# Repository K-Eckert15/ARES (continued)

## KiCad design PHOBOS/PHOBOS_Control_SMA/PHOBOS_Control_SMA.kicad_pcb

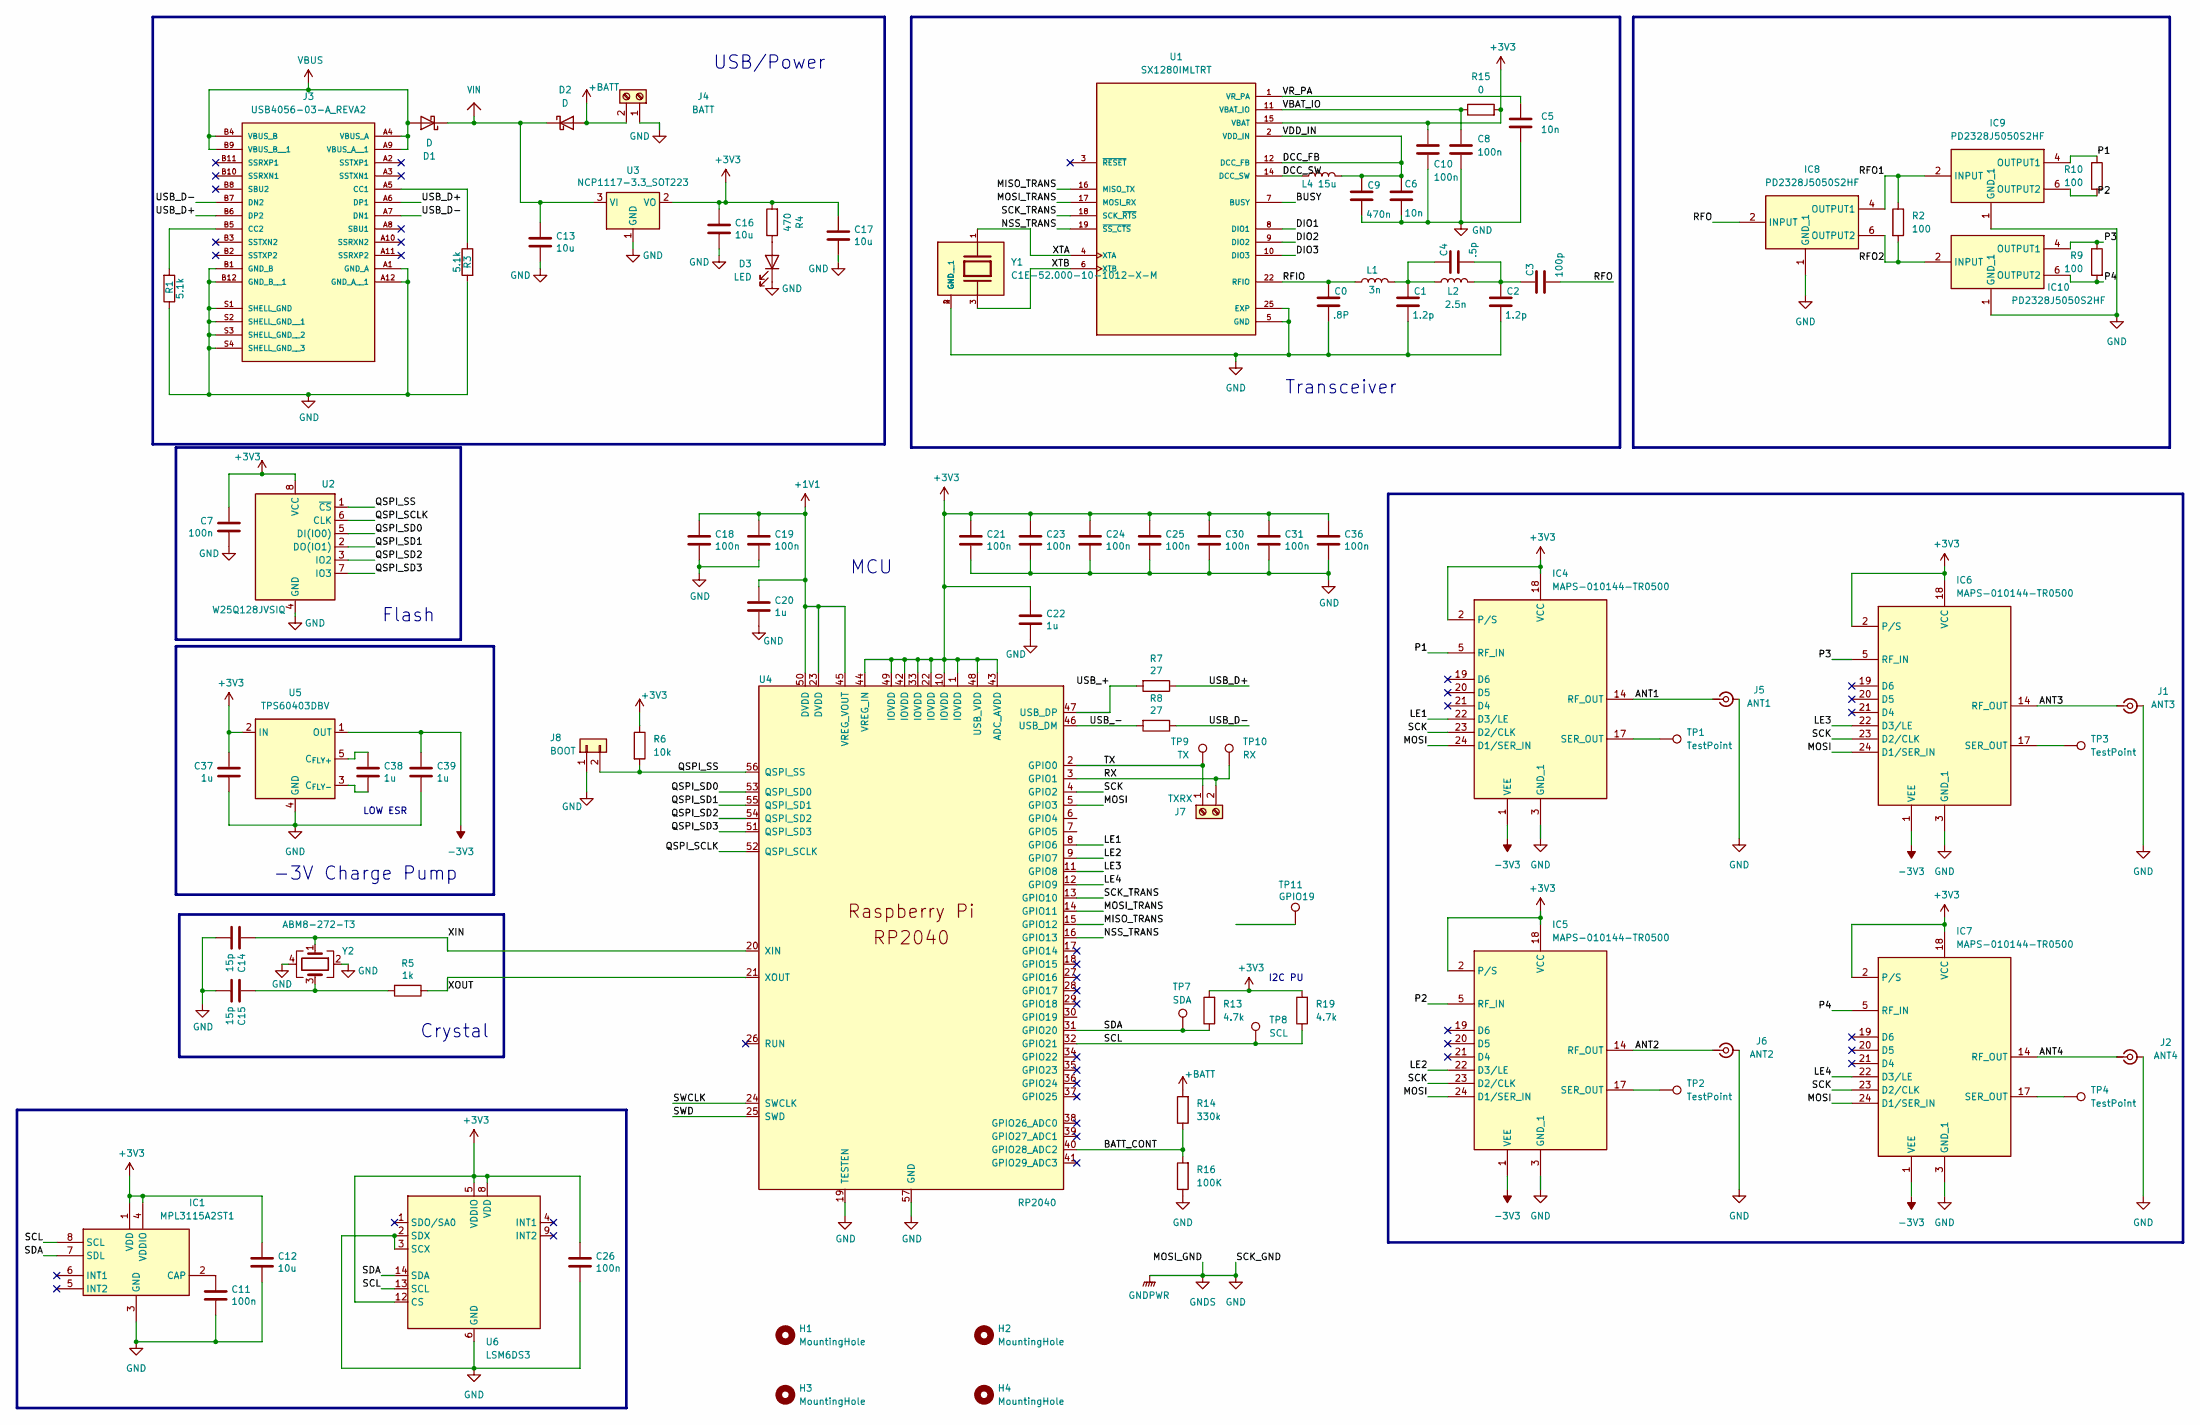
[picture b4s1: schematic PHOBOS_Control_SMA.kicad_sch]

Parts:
C0: .8P; C_0402_1005Metric_Pad0.74x0.62mm_HandSolder; MFG # GRM1555C1HR80BA01D
C1, C2: 1.2p; C_0402_1005Metric_Pad0.74x0.62mm_HandSolder; MFG # GRM1555C1H1R2BA01D
C3: 100p; C_0402_1005Metric_Pad0.74x0.62mm_HandSolder; MFG # GRM1555C1H101JA01D
C4: .5p; C_0402_1005Metric_Pad0.74x0.62mm_HandSolder; MFG # GRM1555C1HR50WA01D
C5, C6: 10n; C_0402_1005Metric_Pad0.74x0.62mm_HandSolder; MFG # GRM155R71E103KA01D
C7, C11, C18, C19, C21, C23, C24, C25, C26, C30, C31, C36: 100n; C_0402_1005Metric; MFG # CL05B104KO5NNNC
C8, C10: 100n; C_0402_1005Metric_Pad0.74x0.62mm_HandSolder; MFG # GRM155R71C104KA88D
C9: 470n; C_0402_1005Metric_Pad0.74x0.62mm_HandSolder; MFG # GRM155R61A474KE15D
C12, C13, C16, C17: 10u; C_0603_1608Metric_Pad1.08x0.95mm_HandSolder; MFG # CL10X106MO8NRNC
C14, C15: 15p; C_0402_1005Metric; MFG # GJM1555C1H150GB01D
C20, C22: 1u; C_0402_1005Metric; MFG # C0603X5R500-105KNP-CT
C37, C38, C39: 1u; C_0603_1608Metric; MFG # C0603X5R500-105KNP-CT
D1, D2: D; D_0603_1608Metric_Pad1.05x0.95mm_HandSolder; MFG # CD0603-B0340R
D3: LED; LED_0603_1608Metric_Pad1.05x0.95mm_HandSolder; MFG # QBLP601-IB5-S2897
H1, H2, H3, H4: MountingHole; MountingHole_3.2mm_M3
IC1: MPL3115A2ST1; Manufacturer_Part_Number MPL3115A2ST1; Mouser Part Number 771-MPL3115A2ST1
IC4, IC5, IC6, IC7: MAPS-010144-TR0500; QFN50P400X400X100-25N-D; Mouser Part Number 937-MAPS-010144T5
IC8, IC9, IC10: PD2328J5050S2HF; Mouser Part Number 620-PD2328J5050S2HF
J1: ANT3; SAMTEC_SMA-J-P-GF-RA-SM1
J2: ANT4; SAMTEC_SMA-J-P-GF-RA-SM1
J3: USB4056-03-A_REVA2; GCT_USB4056-03-A_REVA2; PARTREV A2
J4: BATT; TerminalBlock_4Ucon_1x02_P3.50mm_Horizontal; MFG # OSTTE020104
J5: ANT1; SAMTEC_SMA-J-P-GF-RA-SM1
J6: ANT2; SAMTEC_SMA-J-P-GF-RA-SM1
J7: TXRX; TerminalBlock_4Ucon_1x02_P3.50mm_Horizontal; MFG # OSTTE020104
J8: BOOT; PinHeader_1x02_P2.54mm_Vertical
L1: 3n; L_0402_1005Metric_Pad0.77x0.64mm_HandSolder; MFG # LQW15AN3N0B80D
L2: 2.5n; L_0402_1005Metric_Pad0.77x0.64mm_HandSolder; MFG # LQW15AN2N5C00D
L4: 15u; L_0805_2012Metric_Pad1.05x1.20mm_HandSolder; MFG # MLZ2012M150W
R1, R3: 5.1k; R_0402_1005Metric; MFG # AC0402FR-7W5K1L
R2, R9, R10: 100; R_0603_1608Metric
R4: 470; R_0402_1005Metric; MFG # AC0402FR-7W470RL
R5: 1k; R_0402_1005Metric; MFG # AC0402FR-7W1KL
R6: 10k; R_0402_1005Metric; MFG # AC0402FR-7W10KL
R7, R8: 27; R_0402_1005Metric; MFG # RC0402FR-7W27RL
R13, R19: 4.7k; R_0402_1005Metric; MFG # AC0402FR-7W4K7L
R14: 330k; R_0402_1005Metric; MFG # CRGCQ0402F330K
R15: 0; R_0402_1005Metric_Pad0.72x0.64mm_HandSolder; MFG # CRCW04020000Z0ED
R16: 100K; R_0402_1005Metric; MFG # AC0402FR-7W100KL
TP1, TP2, TP3, TP4: TestPoint; Pin_D1.0mm_L10.0mm
TP7: SDA; TestPoint_THTPad_D2.0mm_Drill1.0mm
TP8: SCL; TestPoint_THTPad_D2.0mm_Drill1.0mm
TP9: TX; TestPoint_THTPad_D2.0mm_Drill1.0mm
TP10: RX; TestPoint_THTPad_D2.0mm_Drill1.0mm
TP11: GPIO19; TestPoint_THTPad_D2.0mm_Drill1.0mm
U1: SX1280IMLTRT; XCVR_SX1280IMLTRT; PARTREV 3.3
U2: W25Q128JVSIQ; SOIC-8_5.3x5.3mm_P1.27mm; MFG # W25Q128JVSIQ
U3: NCP1117-3.3_SOT223; SOT-223-3_TabPin2; MFG # NCP1117ST33T3G
U4: RP2040; QFN-56-1EP_7x7mm_P0.4mm_EP3.2x3.2mm; MFG # SC0914(13)
U5: TPS60403DBV; SOT-23-5; MFG # TPS60403DBV
U6: LSM6DS3; LGA-14_3x2.5mm_P0.5mm_LayoutBorder3x4y
Y1: C1E-52.000-10-1012-X-M; XTAL_C1E-52.000-10-1012-X-M; PARTREV August 01, 2022
Y2: ABM8-272-T3; Crystal_SMD_3225-4Pin_3.2x2.5mm; MFG # ABM8-272-T3

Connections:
+1V1: C18.1, C19.1, C20.1, U4.23 (DVDD), U4.45 (VREG_VOUT), U4.50 (DVDD)
+3V3: C7.1, C10.1, C12.1, C16.1, C17.1, C21.1, C22.1, C23.1, C24.1, C25.1, C26.1, C30.1, C31.1, C36.1, C37.1, IC1.1 (VDD), IC1.4 (VDDIO), IC4.2 (P/S), IC4.18 (VCC), IC5.2 (P/S), IC5.18 (VCC), IC6.2 (P/S), IC6.18 (VCC), IC7.2 (P/S), IC7.18 (VCC), R4.2, R6.1, R13.2, R15.2, R19.2, U1.15 (VBAT), U2.8 (VCC), U3.2 (VO), U4.1 (IOVDD), U4.10 (IOVDD), U4.22 (IOVDD), U4.33 (IOVDD), U4.42 (IOVDD), U4.43 (ADC_AVDD), U4.44 (VREG_IN), U4.48 (USB_VDD), U4.49 (IOVDD), U5.2 (IN), U6.5 (VDDIO), U6.8 (VDD), U6.12 (CS)
+BATT: D2.2 (A), J4.2, R14.2
-3V3: C39.1, IC4.1 (VEE), IC5.1 (VEE), IC6.1 (VEE), IC7.1 (VEE), U5.1 (OUT)
/ANT1: IC4.14 (RF_OUT), J5.1 (In)
/ANT2: IC5.14 (RF_OUT), J6.1 (In)
/ANT3: IC6.14 (RF_OUT), J1.1 (In)
/ANT4: IC7.14 (RF_OUT), J2.1 (In)
/BATT_CONT: R14.1, R16.2, U4.40 (GPIO28_ADC2)
/BUSY: U1.7 (BUSY)
/DCC_FB: C6.1, C9.1, L4.2, U1.2 (VDD_IN), U1.12 (DCC_FB)
/DCC_SW: L4.1, U1.14 (DCC_SW)
/DIO1: U1.8 (DIO1)
/DIO2: U1.9 (DIO2)
/DIO3: U1.10 (DIO3)
/LE1: IC4.22 (D3/LE), U4.8 (GPIO6)
/LE2: IC5.22 (D3/LE), U4.9 (GPIO7)
/LE3: IC6.22 (D3/LE), U4.11 (GPIO8)
/LE4: IC7.22 (D3/LE), U4.12 (GPIO9)
/MISO_TRANS: U1.16 (MISO_TX), U4.15 (GPIO12)
/MOSI: IC4.24 (D1/SER_IN), IC5.24 (D1/SER_IN), IC6.24 (D1/SER_IN), IC7.24 (D1/SER_IN), U4.5 (GPIO3)
/MOSI_TRANS: U1.17 (MOSI_RX), U4.14 (GPIO11)
/NSS_TRANS: U1.19 (~SS_CTS), U4.16 (GPIO13)
/P1: IC4.5 (RF_IN), IC9.4 (OUTPUT1), R10.1
/P2: IC5.5 (RF_IN), IC9.6 (OUTPUT2), R10.2
/P3: IC6.5 (RF_IN), IC10.4 (OUTPUT1), R9.1
/P4: IC7.5 (RF_IN), IC10.6 (OUTPUT2), R9.2
/QSPI_SCLK: U2.6 (CLK), U4.52 (QSPI_SCLK)
/QSPI_SD0: U2.5 (DI(IO0)), U4.53 (QSPI_SD0)
/QSPI_SD1: U2.2 (DO(IO1)), U4.55 (QSPI_SD1)
/QSPI_SD2: U2.3 (IO2), U4.54 (QSPI_SD2)
/QSPI_SD3: U2.7 (IO3), U4.51 (QSPI_SD3)
/QSPI_SS: J8.2, R6.2, U2.1 (~CS), U4.56 (QSPI_SS)
/RFIO: C0.1, L1.1, U1.22 (RFIO)
/RFO: C3.2, IC8.2 (INPUT)
/RFO1: IC8.4 (OUTPUT1), IC9.2 (INPUT), R2.1
/RFO2: IC8.6 (OUTPUT2), IC10.2 (INPUT), R2.2
/RX: J7.2, TP10.1 (1_1), U4.3 (GPIO1)
/SCK: IC4.23 (D2/CLK), IC5.23 (D2/CLK), IC6.23 (D2/CLK), IC7.23 (D2/CLK), U4.4 (GPIO2)
/SCK_TRANS: U1.18 (SCK_~RTS), U4.13 (GPIO10)
/SCL: IC1.8 (SCL), R19.1, TP8.1 (1_1), U4.32 (GPIO21), U6.13 (SCL)
/SDA: IC1.7 (SDL), R13.1, TP7.1 (1_1), U4.31 (GPIO20), U6.14 (SDA)
/SWCLK: U4.24 (SWCLK)
/SWD: U4.25 (SWD)
/TX: J7.1, TP9.1 (1_1), U4.2 (GPIO0)
/USB_+: R7.2, U4.47 (USB_DP)
/USB_-: R8.2, U4.46 (USB_DM)
/USB_D+: J3.A6 (DP1), J3.B6 (DP2), R7.1
/USB_D-: J3.A7 (DN1), J3.B7 (DN2), R8.1
/VBAT_IO: C8.1, R15.1, U1.11 (VBAT_IO)
/VR_PA: C5.1, U1.1 (VR_PA)
/XIN: C14.1, U4.20 (XIN), Y2.1
/XOUT: R5.1, U4.21 (XOUT)
/XTA: U1.4 (XTA), Y1.1
/XTB: U1.6 (XTB), Y1.3
GND: C0.2, C1.2, C2.2, C5.2, C6.2, C7.2, C8.2, C9.2, C10.2, C11.2, C12.2, C13.2, C14.2, C15.2, C16.2, C17.2, C18.2, C19.2, C20.2, C21.2, C22.2, C23.2, C24.2, C25.2, C26.2, C30.2, C31.2, C36.2, C37.2, C39.2, D3.1 (K), IC1.3 (GND), IC4.3 (GND_1), IC4.4 (GND_2), IC4.6 (GND_3), IC4.7 (GND_4), IC4.8 (GND_5), IC4.9 (GND_6), IC4.10 (GND_7), IC4.11 (GND_8), IC4.12 (GND_9), IC4.13 (GND_10), IC4.15 (GND_11), IC4.16 (GND_12), IC4.25 (GND_13), IC5.3 (GND_1), IC5.4 (GND_2), IC5.6 (GND_3), IC5.7 (GND_4), IC5.8 (GND_5), IC5.9 (GND_6), IC5.10 (GND_7), IC5.11 (GND_8), IC5.12 (GND_9), IC5.13 (GND_10), IC5.15 (GND_11), IC5.16 (GND_12), IC5.25 (GND_13), IC6.3 (GND_1), IC6.4 (GND_2), IC6.6 (GND_3), IC6.7 (GND_4), IC6.8 (GND_5), IC6.9 (GND_6), IC6.10 (GND_7), IC6.11 (GND_8), IC6.12 (GND_9), IC6.13 (GND_10), IC6.15 (GND_11), IC6.16 (GND_12), IC6.25 (GND_13), IC7.3 (GND_1), IC7.4 (GND_2), IC7.6 (GND_3), IC7.7 (GND_4), IC7.8 (GND_5), IC7.9 (GND_6), IC7.10 (GND_7), IC7.11 (GND_8), IC7.12 (GND_9), IC7.13 (GND_10), IC7.15 (GND_11), IC7.16 (GND_12), IC7.25 (GND_13), IC8.1 (GND_1), IC8.3 (GND_2), IC8.5 (GND_3), IC9.1 (GND_1), IC9.3 (GND_2), IC9.5 (GND_3), IC10.1 (GND_1), IC10.3 (GND_2), IC10.5 (GND_3), J1.2 (Ext), J2.2 (Ext), J3.A1 (GND_A), J3.A12 (GND_A__1), J3.B1 (GND_B), J3.B12 (GND_B__1), J3.S1 (SHELL_GND), J3.S2 (SHELL_GND__1), J3.S3 (SHELL_GND__2), J3.S4 (SHELL_GND__3), J4.1, J5.2 (Ext), J6.2 (Ext), J8.1, R1.1, R3.2, R16.1, U1.5 (GND), U1.13 (GND), U1.20 (GND), U1.21 (GND), U1.23 (GND), U1.24 (GND), U1.25 (EXP), U2.4 (GND), U3.1 (GND), U4.19 (TESTEN), U4.57 (GND), U5.4 (GND), U6.2 (SDX), U6.3 (SCX), U6.6 (GND), U6.7 (GND), Y1.2 (GND), Y1.4 (GND__1), Y2.2, Y2.4
unnamed: C1.1, C4.1, L1.2, L2.1
unnamed: C2.1, C3.1, C4.2, L2.2
unnamed: C15.1, R5.2, Y2.3
unnamed: D3.2 (A), R4.1
unnamed: C11.1, IC1.2 (CAP)
unnamed: IC4.17 (SER_OUT), TP1.1
unnamed: IC5.17 (SER_OUT), TP2.1
unnamed: IC6.17 (SER_OUT), TP3.1
unnamed: IC7.17 (SER_OUT), TP4.1
unnamed: J3.A5 (CC1), R3.1
unnamed: J3.B5 (CC2), R1.2
unnamed: C38.1, U5.5 (C_{FLY+})
unnamed: C38.2, U5.3 (C_{FLY-})
VBUS: D1.2 (A), J3.A4 (VBUS_A), J3.A9 (VBUS_A__1), J3.B4 (VBUS_B), J3.B9 (VBUS_B__1)
VIN: C13.1, D1.1 (K), D2.1 (K), U3.3 (VI)

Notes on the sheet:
Transceiver
-3V Charge Pump
LOW ESR
Flash
Crystal
MCU
I2C PU
USB/Power

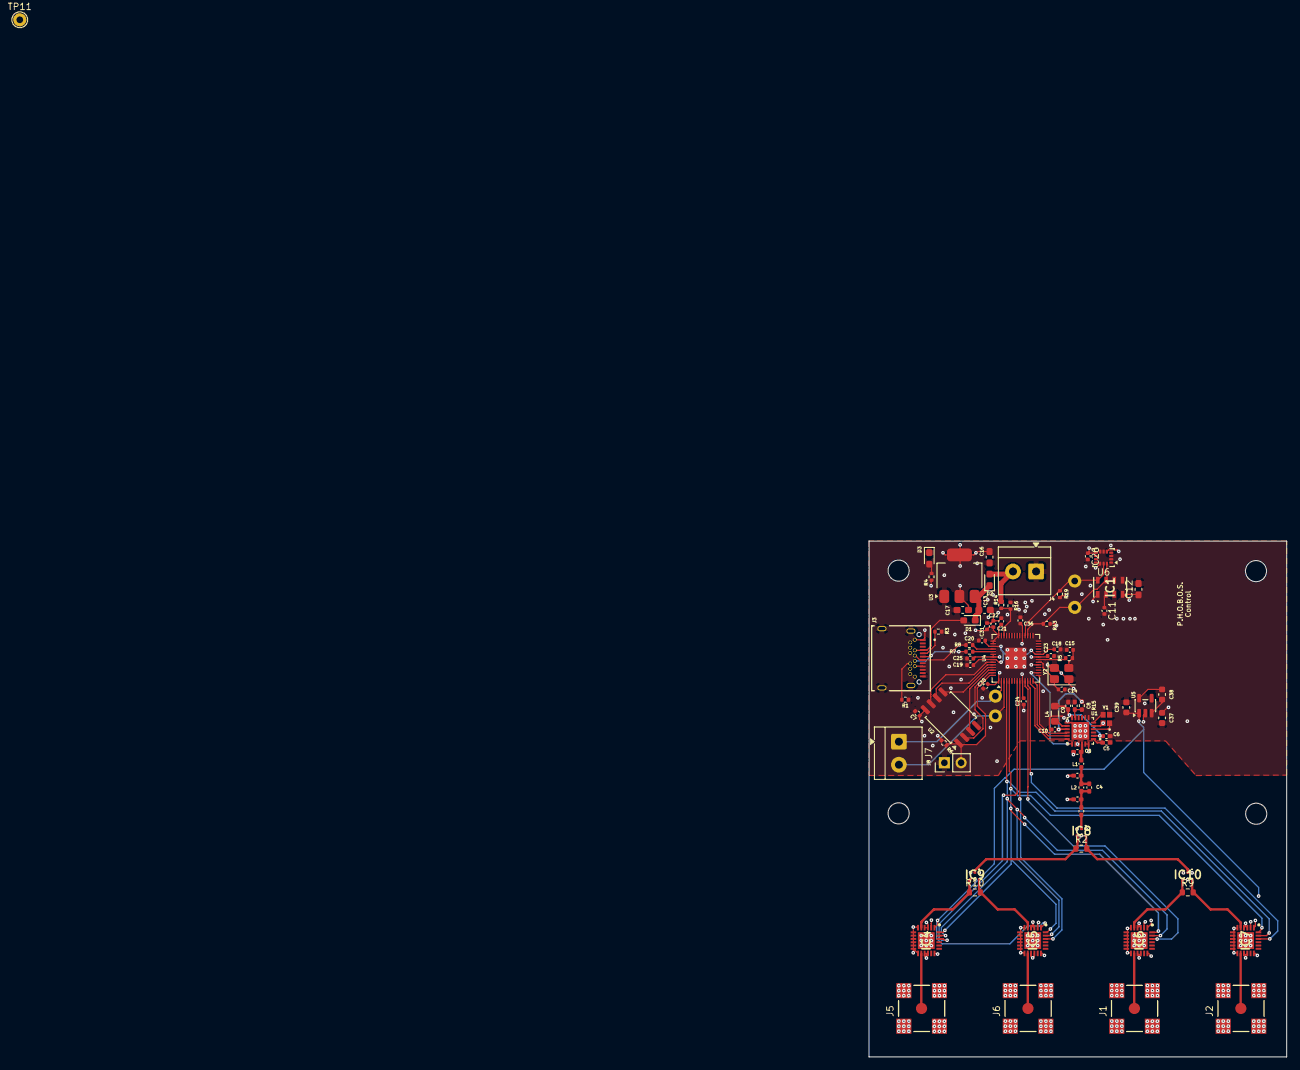
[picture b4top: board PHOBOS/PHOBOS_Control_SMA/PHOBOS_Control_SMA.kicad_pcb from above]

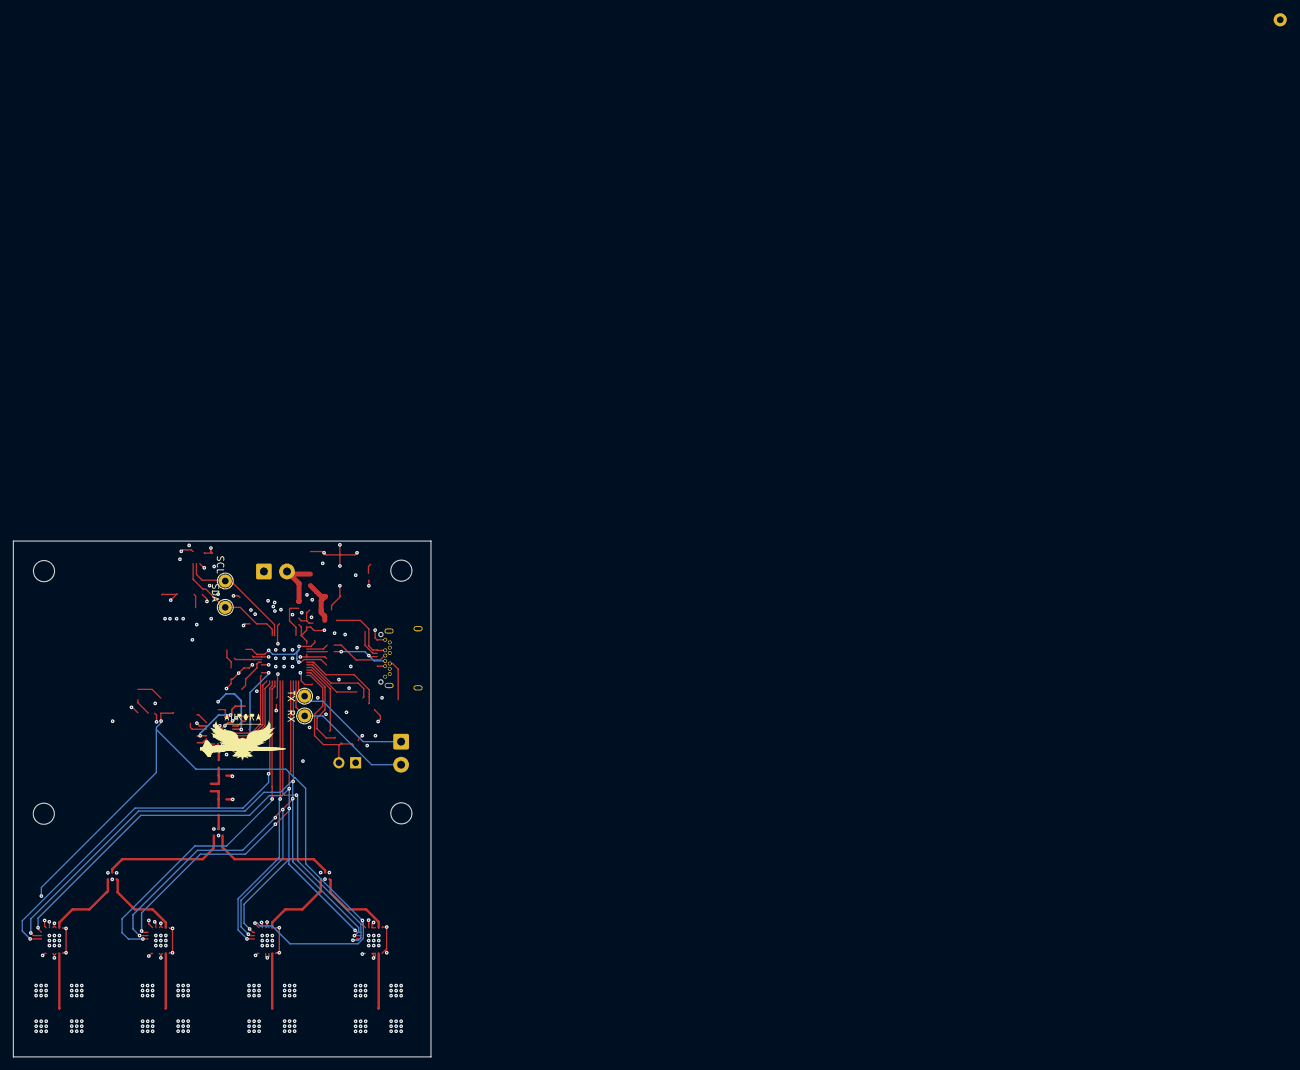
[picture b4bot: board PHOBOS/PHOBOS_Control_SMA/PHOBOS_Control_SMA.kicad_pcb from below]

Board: 4 copper layers, 63.4 x 78.3 mm, 87 parts (4 on the bottom side), 61 nets.

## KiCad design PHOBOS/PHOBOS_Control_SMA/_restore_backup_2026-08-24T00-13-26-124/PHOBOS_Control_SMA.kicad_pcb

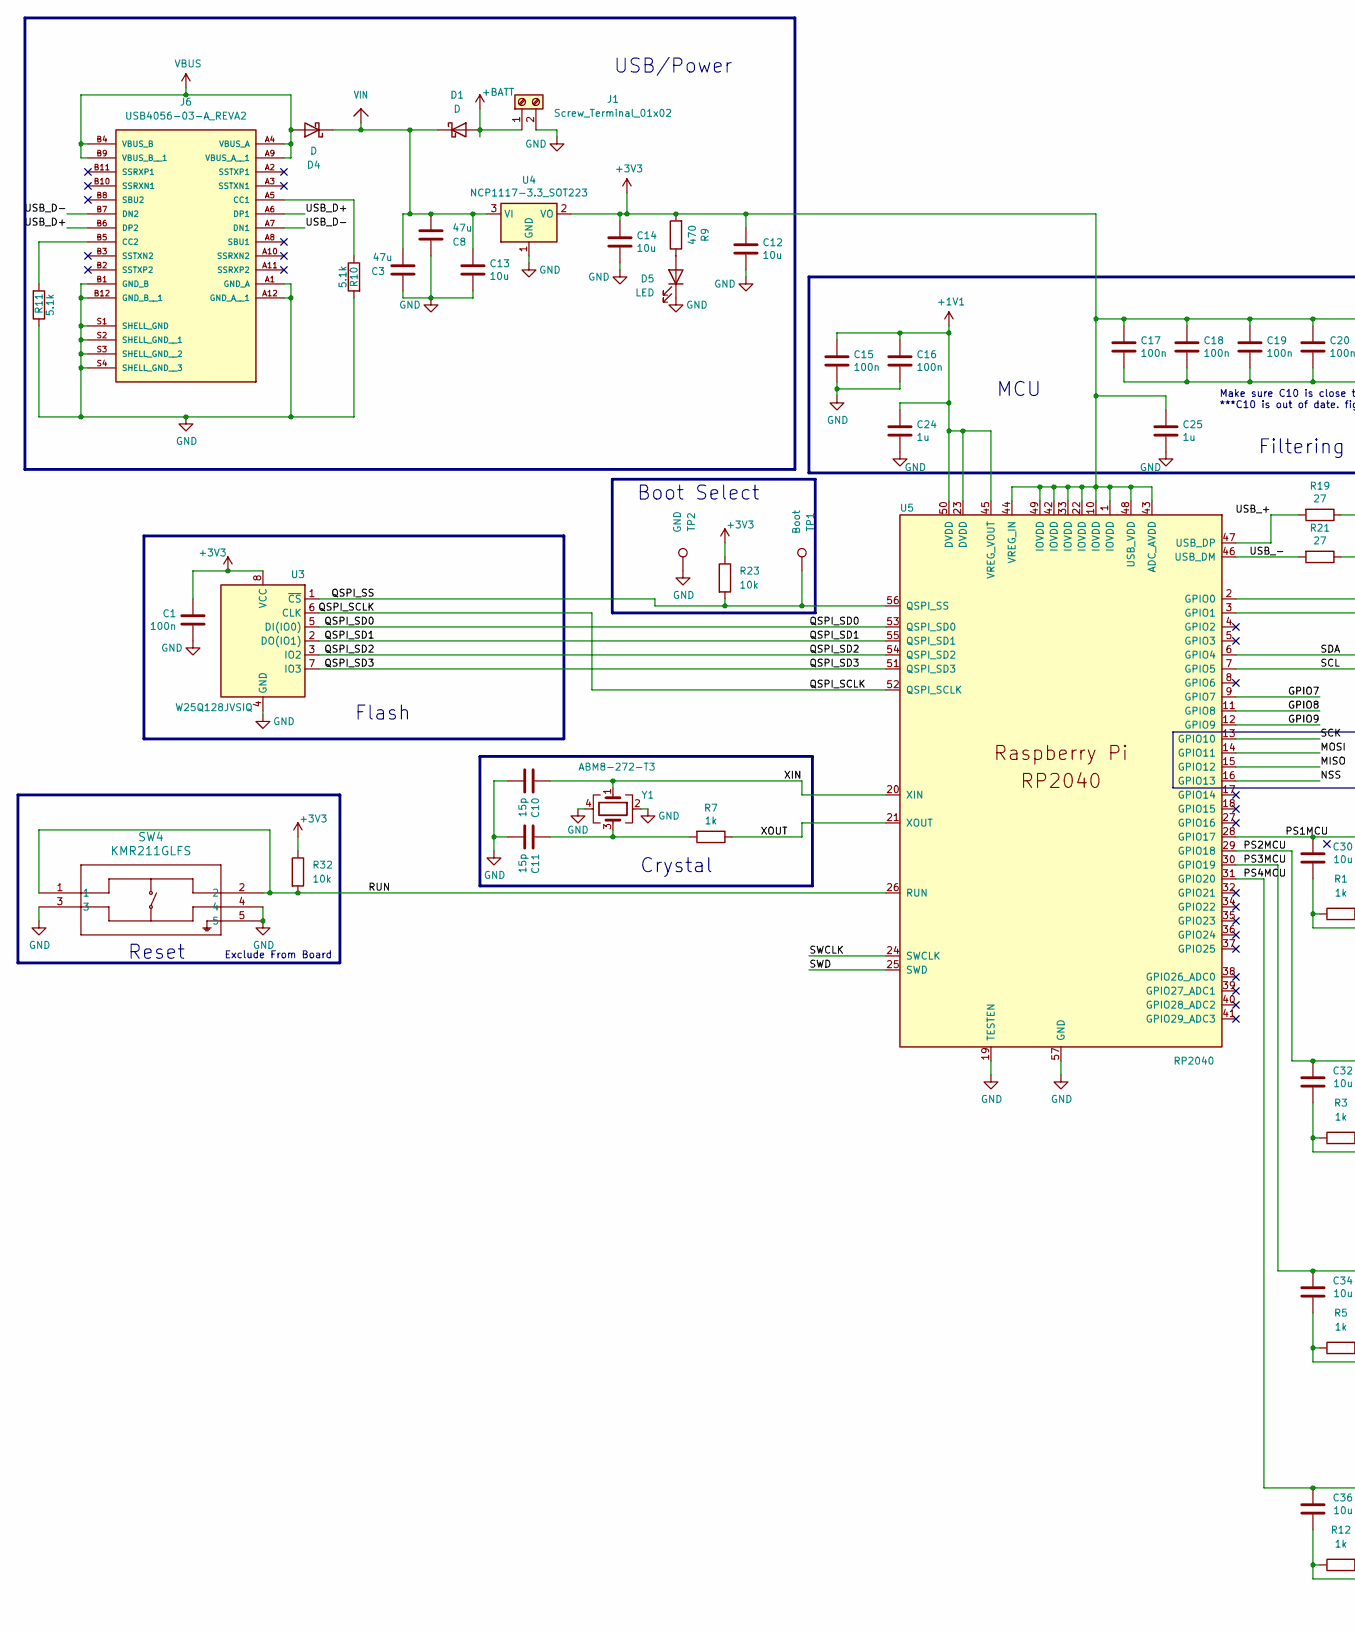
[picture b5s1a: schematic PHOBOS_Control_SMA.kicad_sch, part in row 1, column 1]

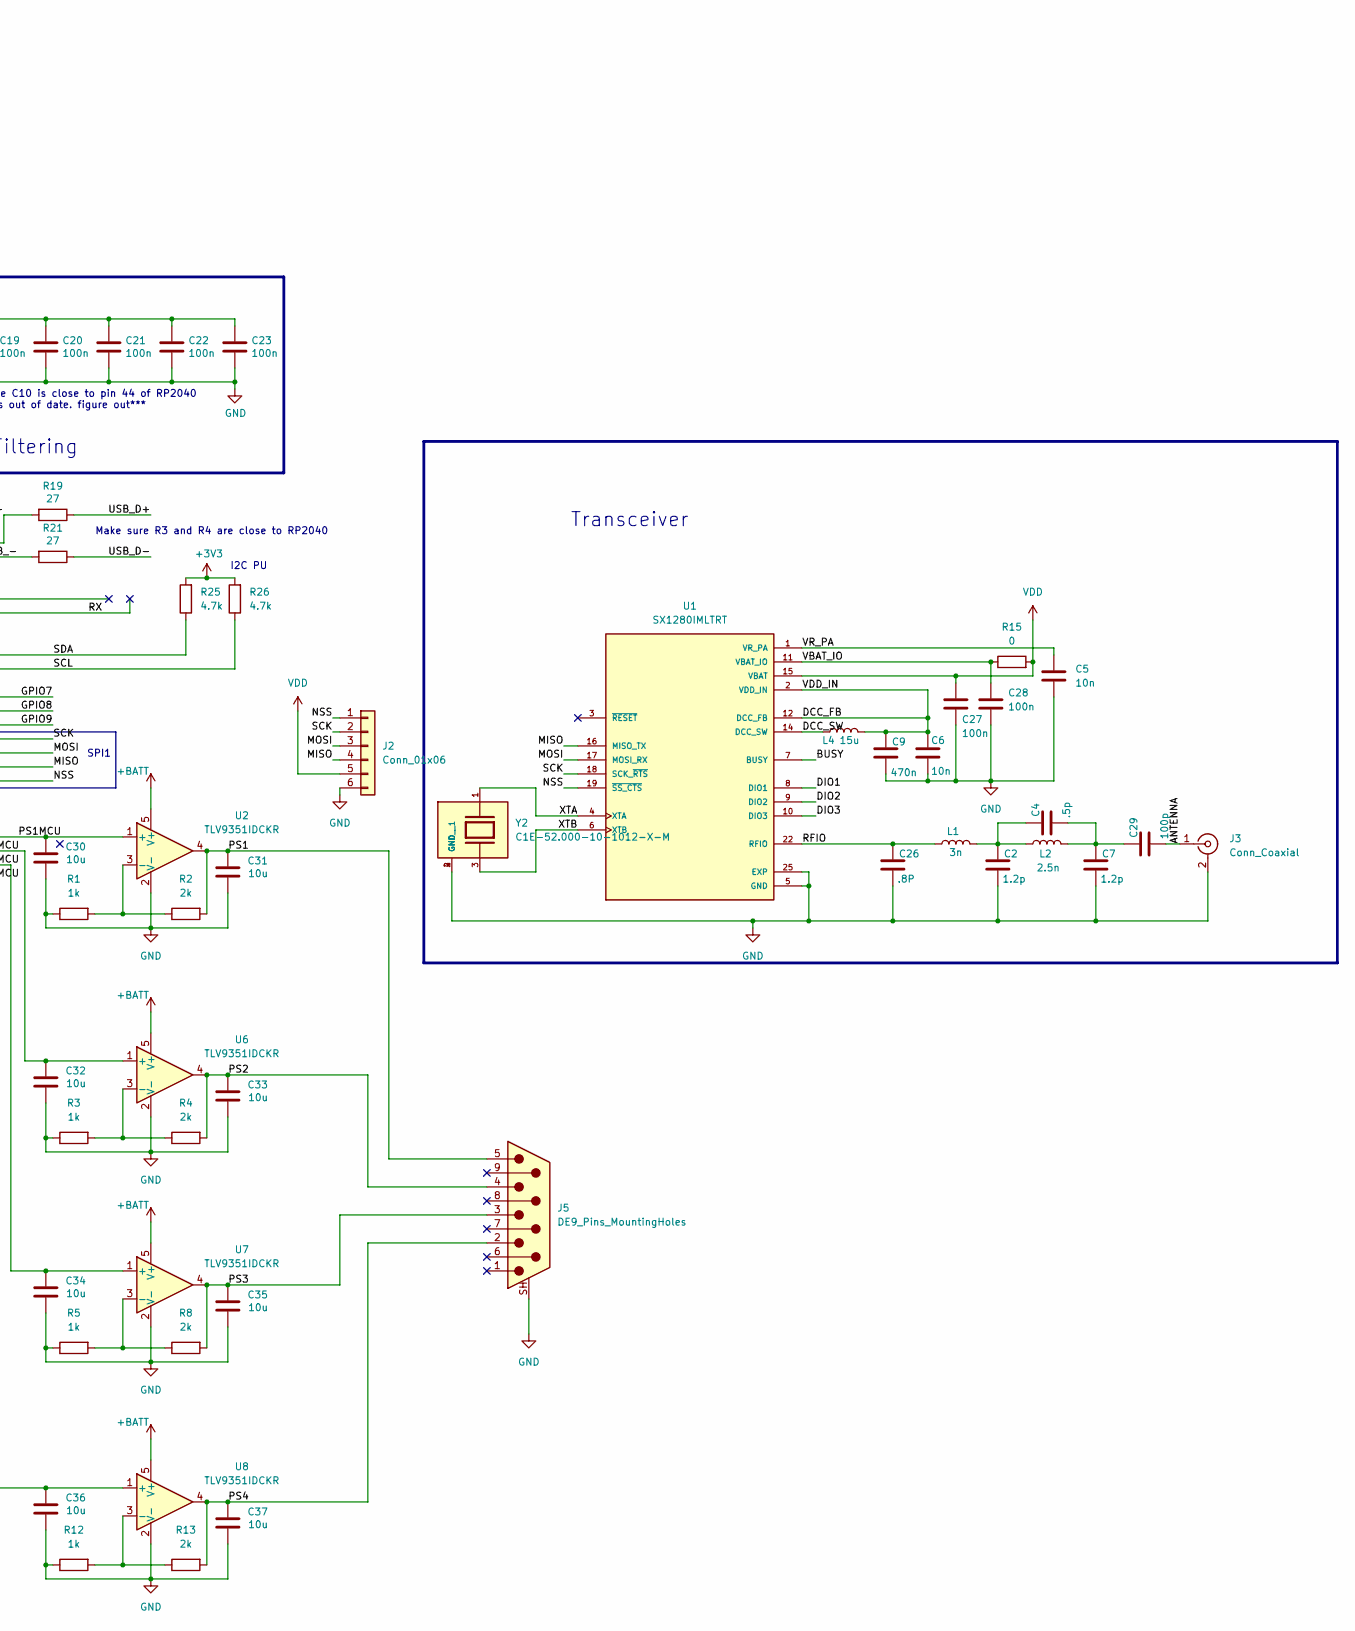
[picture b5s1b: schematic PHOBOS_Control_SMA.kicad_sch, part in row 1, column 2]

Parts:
C1, C15, C16, C17, C18, C19, C20, C21, C22, C23: 100n; C_0402_1005Metric
C2, C7: 1.2p; C_0402_1005Metric_Pad0.74x0.62mm_HandSolder; MFG # GRM1555C1H1R2BA01D
C3: 47u; C_0805_2012Metric_Pad1.18x1.45mm_HandSolder
C4: .5p; C_0402_1005Metric_Pad0.74x0.62mm_HandSolder; MFG # GRM1555C1HR50WA01D
C5, C6: 10n; C_0402_1005Metric_Pad0.74x0.62mm_HandSolder; MFG # GRM155R71E103KA01D
C8: 47u; C_1206_3216Metric
C9: 470n; C_0402_1005Metric_Pad0.74x0.62mm_HandSolder; MFG # GRM155R61A474KE15D
C10, C11: 15p; C_0402_1005Metric
C12, C13, C14: 10u; C_0603_1608Metric_Pad1.08x0.95mm_HandSolder
C24, C25: 1u; C_0402_1005Metric
C26: .8P; C_0402_1005Metric_Pad0.74x0.62mm_HandSolder; MFG # GRM1555C1HR80BA01D
C27, C28: 100n; C_0402_1005Metric_Pad0.74x0.62mm_HandSolder; MFG # GRM155R71C104KA88D
C29: 100p; C_0402_1005Metric_Pad0.74x0.62mm_HandSolder; MFG # GRM1555C1H101JA01D
C30, C31, C32, C33, C34, C35, C36, C37: 10u; C_0402_1005Metric
D1, D4: D; D_0603_1608Metric_Pad1.05x0.95mm_HandSolder
D5: LED; LED_0603_1608Metric_Pad1.05x0.95mm_HandSolder
J1: Screw_Terminal_01x02; TerminalBlock_4Ucon_1x02_P3.50mm_Horizontal
J2: Conn_01x06; PinHeader_1x06_P2.54mm_Vertical
J3: Conn_Coaxial; SAMTEC_SMA-J-P-GF-RA-SM1; MFG # CONSMA001-SMD-G-T
J5: DE9_Pins_MountingHoles; DSUB-9_Pins_Horizontal_P2.77x2.84mm_EdgePinOffset7.70mm_Hou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; MFG # 6E17C009SAJ120
J6: USB4056-03-A_REVA2; GCT_USB4056-03-A_REVA2; PARTREV A2
L1: 3n; L_0402_1005Metric_Pad0.77x0.64mm_HandSolder; MFG # LQW15AN3N0B80D
L2: 2.5n; L_0402_1005Metric_Pad0.77x0.64mm_HandSolder; MFG # LQW15AN2N5C00D
L4: 15u; L_0805_2012Metric_Pad1.05x1.20mm_HandSolder; MFG # MLZ2012M150W
R1, R3, R5, R12: 1k; R_0402_1005Metric_Pad0.72x0.64mm_HandSolder
R2, R4, R8, R13: 2k; R_0402_1005Metric_Pad0.72x0.64mm_HandSolder
R7: 1k; R_0402_1005Metric
R9: 470; R_0402_1005Metric
R10, R11: 5.1k; R_0402_1005Metric
R15: 0; R_0402_1005Metric_Pad0.72x0.64mm_HandSolder; MFG # CRCW04020000Z0ED
R19, R21: 27; R_0402_1005Metric
R23, R32: 10k; R_0402_1005Metric
R25, R26: 4.7k; R_0402_1005Metric
SW4: KMR211GLFS; KMR2xxG_CNK
TP1: Boot; TestPoint_Pad_D1.0mm
TP2: GND; TestPoint_Pad_D1.0mm
U1: SX1280IMLTRT; XCVR_SX1280IMLTRT; PARTREV 3.3
U2, U6, U7, U8: TLV9351IDCKR; SOT-353_SC-70-5
U3: W25Q128JVSIQ; SOIC-8_5.3x5.3mm_P1.27mm
U4: NCP1117-3.3_SOT223; SOT-223-3_TabPin2
U5: RP2040; QFN-56-1EP_7x7mm_P0.4mm_EP3.2x3.2mm
Y1: ABM8-272-T3; Crystal_SMD_3225-4Pin_3.2x2.5mm
Y2: C1E-52.000-10-1012-X-M; XTAL_C1E-52.000-10-1012-X-M; PARTREV August 01, 2022

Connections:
+1V1: C15.1, C16.1, C24.1, U5.23 (DVDD), U5.45 (VREG_VOUT), U5.50 (DVDD)
+3V3: C1.1, C12.1, C14.1, C17.1, C18.1, C19.1, C20.1, C21.1, C22.1, C23.1, C25.1, R9.2, R23.1, R25.2, R26.2, R32.1, U3.8 (VCC), U4.2 (VO), U5.1 (IOVDD), U5.10 (IOVDD), U5.22 (IOVDD), U5.33 (IOVDD), U5.42 (IOVDD), U5.43 (ADC_AVDD), U5.44 (VREG_IN), U5.48 (USB_VDD), U5.49 (IOVDD)
+BATT: D1.2 (A), J1.1, U2.5 (V+), U6.5 (V+), U7.5 (V+), U8.5 (V+)
/ANTENNA: C29.2, J3.1 (In)
/BUSY: U1.7 (BUSY)
/DCC_FB: C6.1, C9.1, L4.2, U1.2 (VDD_IN), U1.12 (DCC_FB)
/DCC_SW: L4.1, U1.14 (DCC_SW)
/DIO1: U1.8 (DIO1)
/DIO2: U1.9 (DIO2)
/DIO3: U1.10 (DIO3)
/GPIO7: U5.9 (GPIO7)
/GPIO8: U5.11 (GPIO8)
/GPIO9: U5.12 (GPIO9)
/MISO: J2.4, U1.16 (MISO_TX), U5.15 (GPIO12)
/MOSI: J2.3, U1.17 (MOSI_RX), U5.14 (GPIO11)
/NSS: J2.1, U1.19 (~SS_CTS), U5.16 (GPIO13)
/PS1: C31.1, J5.5, R2.2, U2.4
/PS1MCU: C30.1, U2.1 (+), U5.28 (GPIO17)
/PS2: C33.1, J5.4, R4.2, U6.4
/PS2MCU: C32.1, U5.29 (GPIO18), U6.1 (+)
/PS3: C35.1, J5.3, R8.2, U7.4
/PS3MCU: C34.1, U5.30 (GPIO19), U7.1 (+)
/PS4: C37.1, J5.2, R13.2, U8.4
/PS4MCU: C36.1, U5.31 (GPIO20), U8.1 (+)
/QSPI_SCLK: U3.6 (CLK), U5.52 (QSPI_SCLK)
/QSPI_SD0: U3.5 (DI(IO0)), U5.53 (QSPI_SD0)
/QSPI_SD1: U3.2 (DO(IO1)), U5.55 (QSPI_SD1)
/QSPI_SD2: U3.3 (IO2), U5.54 (QSPI_SD2)
/QSPI_SD3: U3.7 (IO3), U5.51 (QSPI_SD3)
/QSPI_SS: R23.2, TP1.1 (1_1), U3.1 (~CS), U5.56 (QSPI_SS)
/RFIO: C26.1, L1.1, U1.22 (RFIO)
/RUN: R32.2, SW4.1, SW4.2, U5.26 (RUN)
/RX: U5.3 (GPIO1)
/SCK: J2.2, U1.18 (SCK_~RTS), U5.13 (GPIO10)
/SCL: R26.1, U5.7 (GPIO5)
/SDA: R25.1, U5.6 (GPIO4)
/SWCLK: U5.24 (SWCLK)
/SWD: U5.25 (SWD)
/USB_+: R19.2, U5.47 (USB_DP)
/USB_-: R21.2, U5.46 (USB_DM)
/USB_D+: J6.A6 (DP1), J6.B6 (DP2), R19.1
/USB_D-: J6.A7 (DN1), J6.B7 (DN2), R21.1
/VBAT_IO: C28.1, R15.1, U1.11 (VBAT_IO)
/VR_PA: C5.1, U1.1 (VR_PA)
/XIN: C10.1, U5.20 (XIN), Y1.1
/XOUT: R7.1, U5.21 (XOUT)
/XTA: U1.4 (XTA), Y2.1
/XTB: U1.6 (XTB), Y2.3
GND: C1.2, C2.2, C3.1, C5.2, C6.2, C7.2, C8.1, C9.2, C10.2, C11.2, C12.2, C13.2, C14.2, C15.2, C16.2, C17.2, C18.2, C19.2, C20.2, C21.2, C22.2, C23.2, C24.2, C25.2, C26.2, C27.2, C28.2, C30.2, C31.2, C32.2, C33.2, C34.2, C35.2, C36.2, C37.2, D5.1 (K), J1.2, J2.6, J3.2 (Ext), J3.3 (Ext), J3.4 (Ext), J3.5 (Ext), J5.SH (PAD), J6.A1 (GND_A), J6.A12 (GND_A__1), J6.B1 (GND_B), J6.B12 (GND_B__1), J6.S1 (SHELL_GND), J6.S2 (SHELL_GND__1), J6.S3 (SHELL_GND__2), J6.S4 (SHELL_GND__3), R1.1, R3.1, R5.1, R10.2, R11.1, R12.1, SW4.3, SW4.4, SW4.5, TP2.1 (1_1), U1.5 (GND), U1.13 (GND), U1.20 (GND), U1.21 (GND), U1.23 (GND), U1.24 (GND), U1.25 (EXP), U2.2 (V-), U3.4 (GND), U4.1 (GND), U5.19 (TESTEN), U5.57 (GND), U6.2 (V-), U7.2 (V-), U8.2 (V-), Y1.2, Y1.4, Y2.2 (GND), Y2.4 (GND__1)
unnamed: C2.1, C4.1, L1.2, L2.1
unnamed: C11.1, R7.2, Y1.3
unnamed: C4.2, C7.1, C29.1, L2.2
unnamed: D5.2 (A), R9.1
unnamed: J6.A5 (CC1), R10.1
unnamed: J6.B5 (CC2), R11.2
unnamed: R1.2, R2.1, U2.3 (-)
unnamed: R3.2, R4.1, U6.3 (-)
unnamed: R5.2, R8.1, U7.3 (-)
unnamed: R12.2, R13.1, U8.3 (-)
VBUS: D4.2 (A), J6.A4 (VBUS_A), J6.A9 (VBUS_A__1), J6.B4 (VBUS_B), J6.B9 (VBUS_B__1)
VDD: C27.1, J2.5, R15.2, U1.15 (VBAT)
VIN: C3.2, C8.2, C13.1, D1.1 (K), D4.1 (K), U4.3 (VI)

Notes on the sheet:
SPI1
I2C PU
Make sure C10 is close to pin 44 of RP2040 ***C10 is out of date. figure out***
Transceiver
Boot Select
Make sure R3 and R4 are close to RP2040
Reset
Exclude From Board
Flash
Crystal
MCU
Filtering
USB/Power

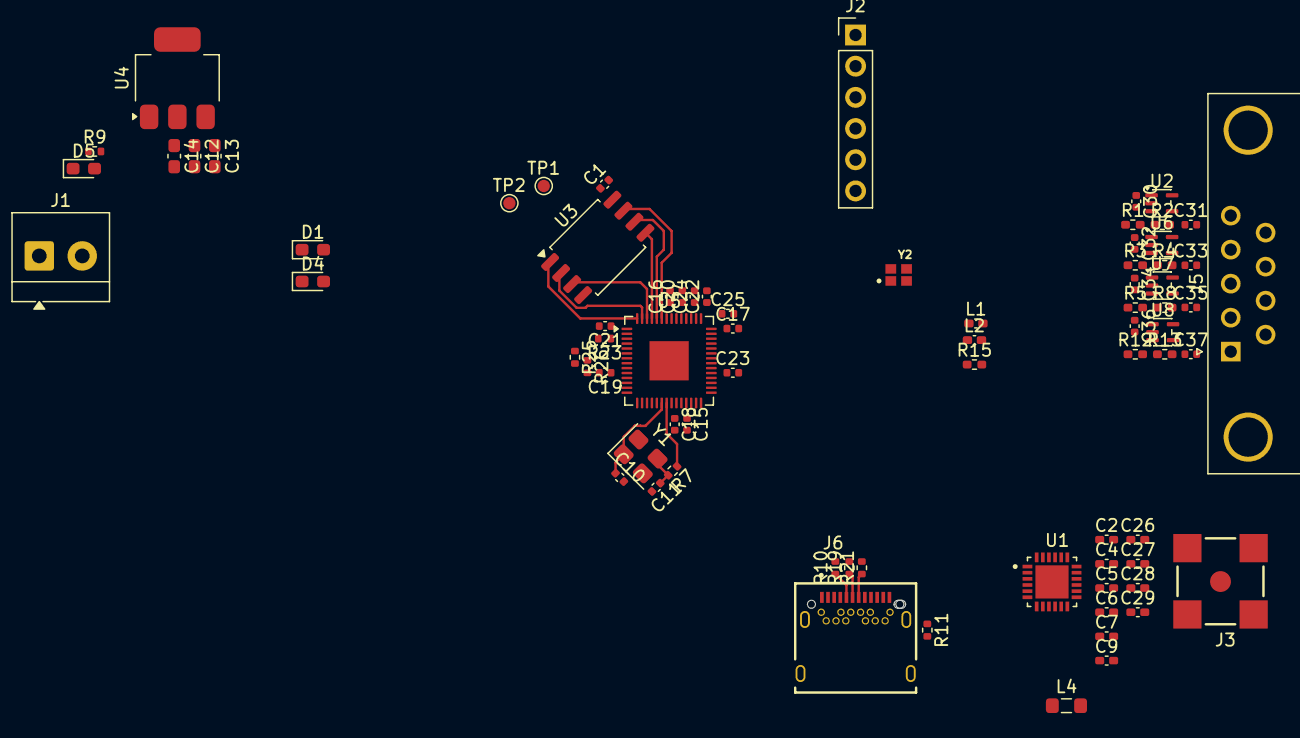
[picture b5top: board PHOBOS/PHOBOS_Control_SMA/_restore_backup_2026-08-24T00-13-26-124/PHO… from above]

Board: 2 copper layers, 76 parts (0 on the bottom side), 51 nets.

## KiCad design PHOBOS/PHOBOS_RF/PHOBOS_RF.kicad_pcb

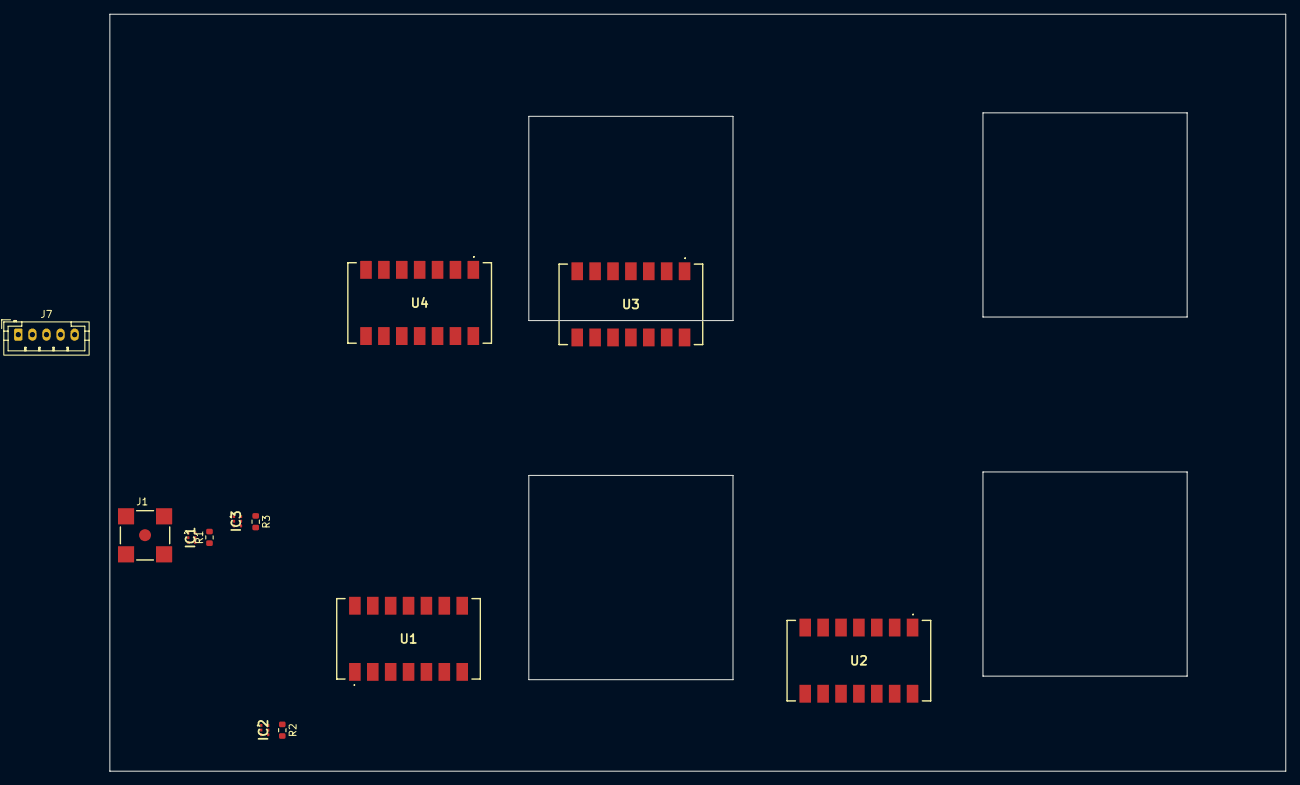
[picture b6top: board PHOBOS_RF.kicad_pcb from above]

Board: 2 copper layers, 167.0 x 107.5 mm, 12 parts (0 on the bottom side), 12 nets, no tracks yet.

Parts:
IC1, IC2, IC3: PD2328J5050S2HF
J1: RF_IN; SAMTEC_SMA-J-P-GF-RA-SM1
J7: Conn_01x05; JST_PH_B5B-PH-K_1x05_P2.00mm_Vertical
R1, R2, R3: 100; R_0603_1608Metric
U1, U2, U3, U4: JSPHS2484

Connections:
/P1: IC2.4 (OUTPUT1), R2.1, U1.1 (RF_IN)
/P2: IC2.6 (OUTPUT2), R2.2, U2.1 (RF_IN)
/P3: IC3.4 (OUTPUT1), R3.1, U3.1 (RF_IN)
/P4: IC3.6 (OUTPUT2), R3.2, U4.1 (RF_IN)
/PS1: J7.1, U1.4 (BIAS), U1.6 (BIAS)
/PS2: J7.2, U2.4 (BIAS), U2.6 (BIAS)
/PS3: J7.3, U3.4 (BIAS), U3.6 (BIAS)
/PS4: J7.4, U4.4 (BIAS), U4.6 (BIAS)
/RF_IN: IC1.2 (INPUT), J1.1 (In)
/S1_OUT1: IC1.4 (OUTPUT1), IC2.2 (INPUT), R1.1
/S1_OUT2: IC1.6 (OUTPUT2), IC3.2 (INPUT), R1.2
GND: IC1.1 (GND_1), IC1.3 (GND_2), IC1.5 (GND_3), IC2.1 (GND_1), IC2.3 (GND_2), IC2.5 (GND_3), IC3.1 (GND_1), IC3.3 (GND_2), IC3.5 (GND_3), J1.2 (Ext), J1.3, J1.4, J1.5, J7.5, U1.2 (GND), U1.3 (GND), U1.5 (GND), U1.8 (GND), U1.9 (GND), U1.10 (GND), U1.11 (GND), U1.12 (GND), U1.13 (GND), U1.14 (GND), U2.2 (GND), U2.3 (GND), U2.5 (GND), U2.8 (GND), U2.9 (GND), U2.10 (GND), U2.11 (GND), U2.12 (GND), U2.13 (GND), U2.14 (GND), U3.2 (GND), U3.3 (GND), U3.5 (GND), U3.8 (GND), U3.9 (GND), U3.10 (GND), U3.11 (GND), U3.12 (GND), U3.13 (GND), U3.14 (GND), U4.2 (GND), U4.3 (GND), U4.5 (GND), U4.8 (GND), U4.9 (GND), U4.10 (GND), U4.11 (GND), U4.12 (GND), U4.13 (GND), U4.14 (GND)
